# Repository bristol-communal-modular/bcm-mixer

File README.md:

# Mixer

A general purpose mixer with two mono input channels and one stereo channel.

Mono Inputs have a gain control with up to 34dB of amplification and a pan control.

Expansion header on the rear will allow additional channels to be incorporated as needed.

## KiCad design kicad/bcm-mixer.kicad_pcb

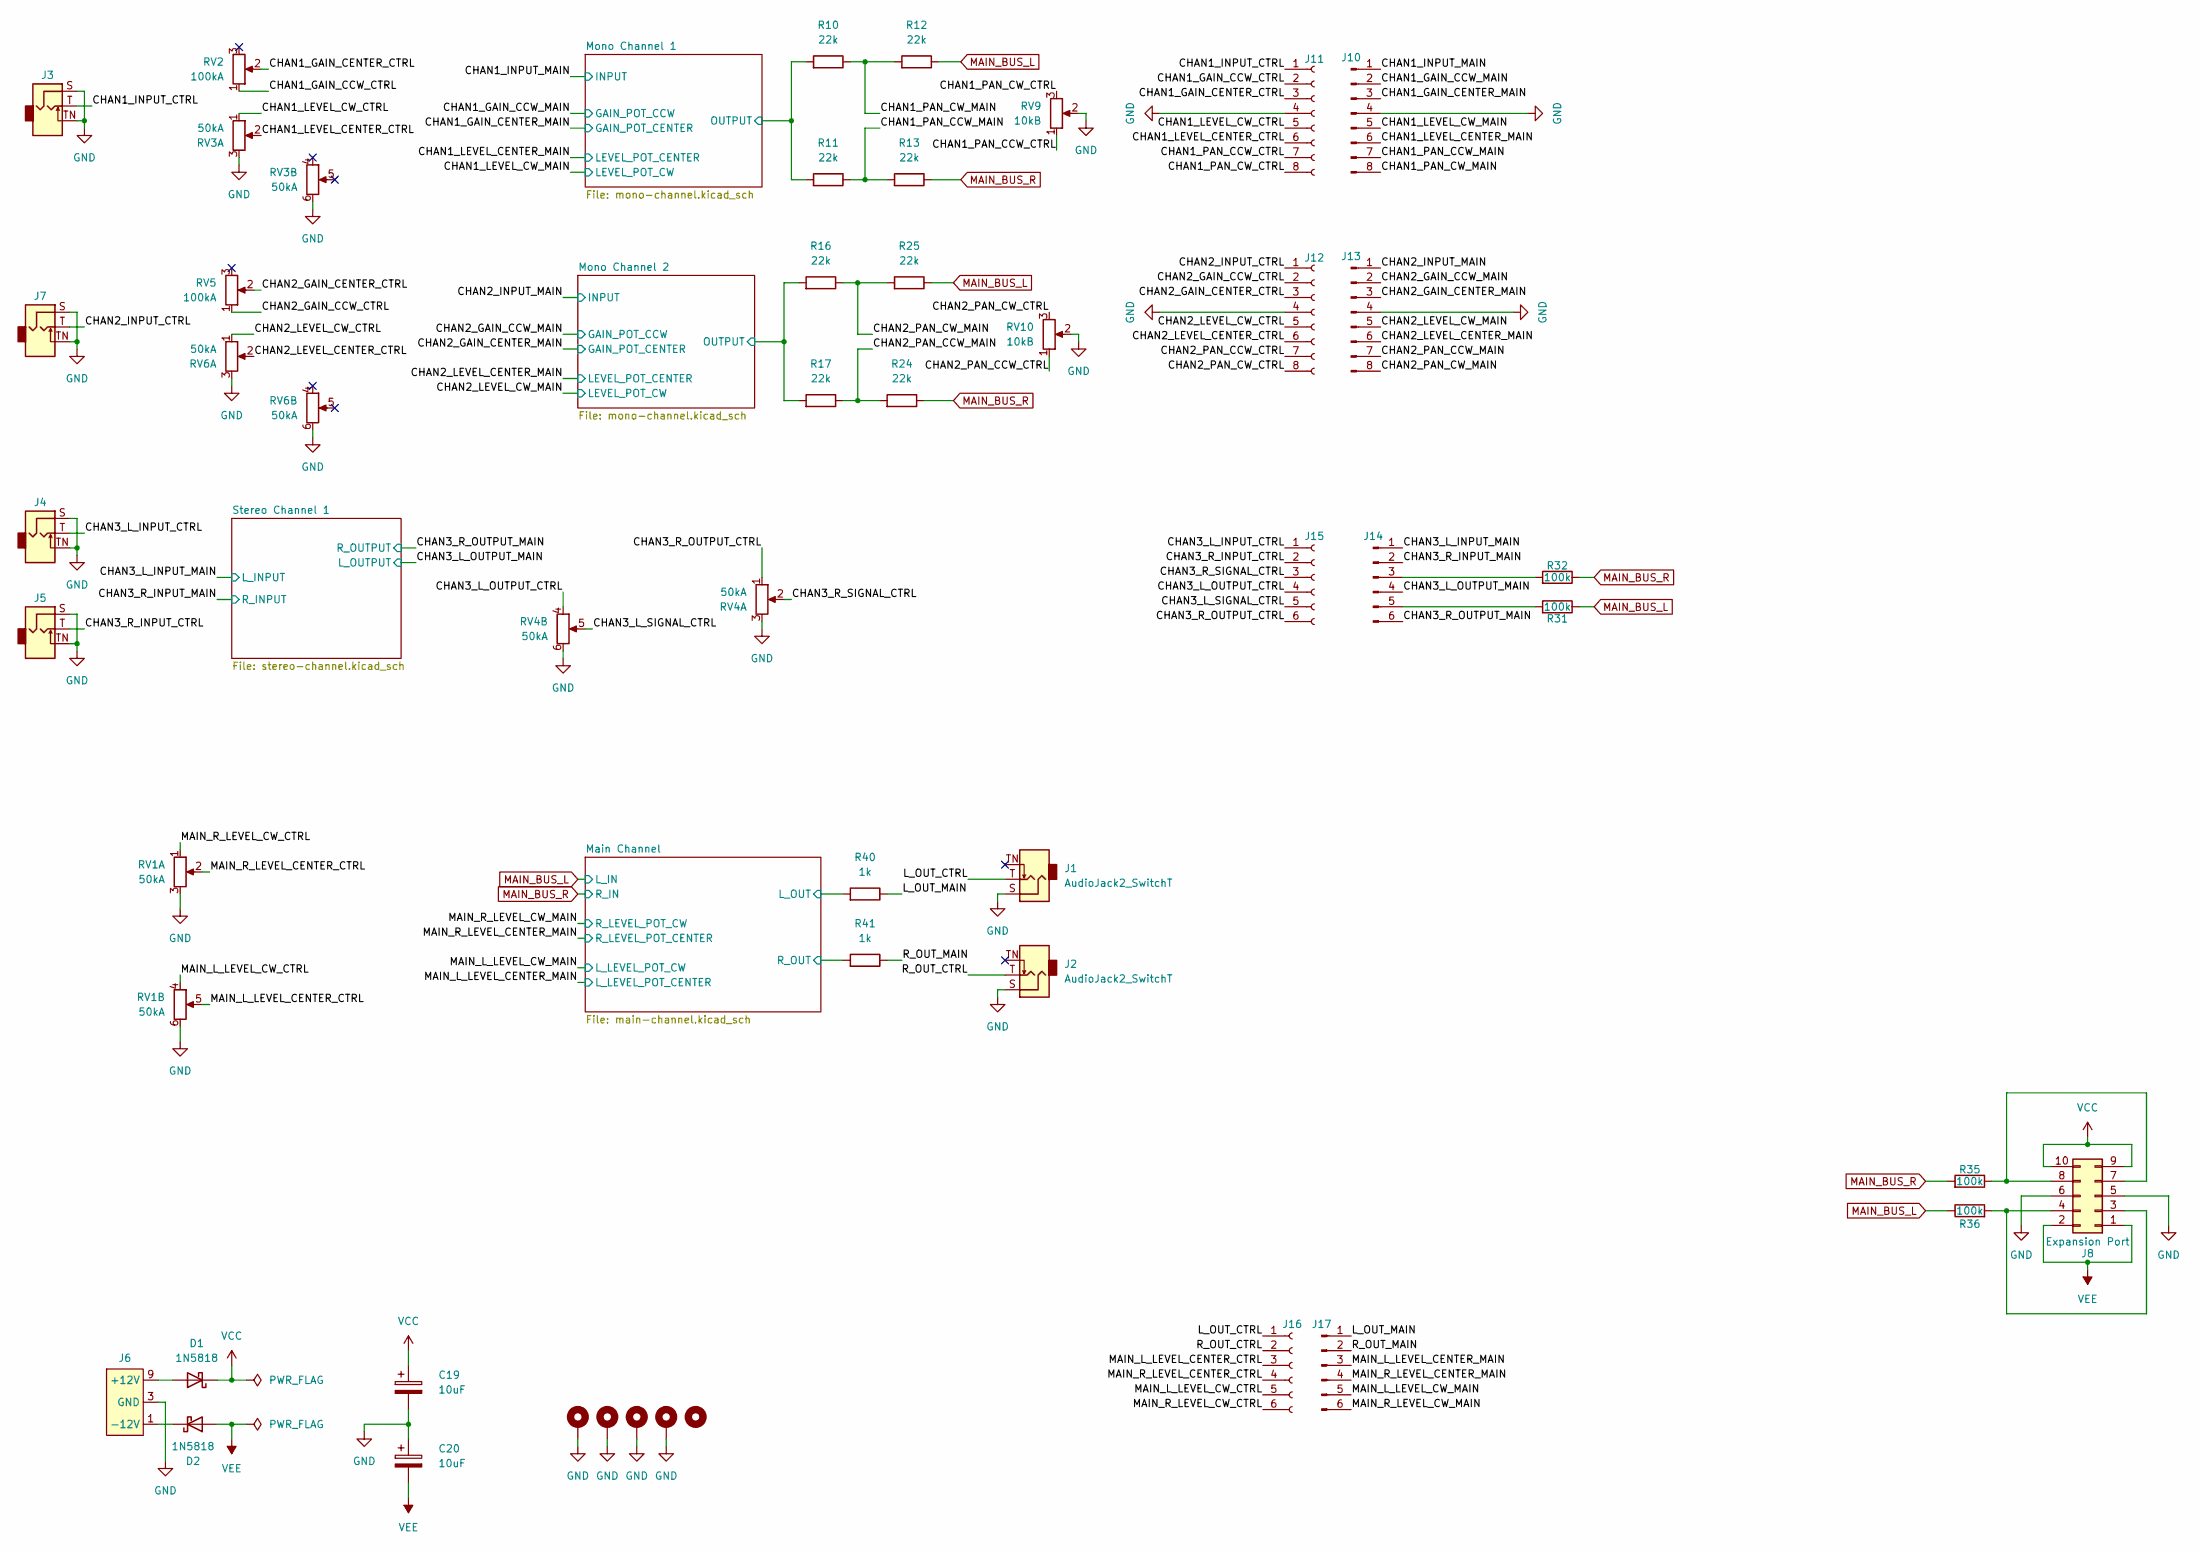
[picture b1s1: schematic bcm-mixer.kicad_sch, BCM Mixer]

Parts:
C19, C20: 10uF; CP_Radial_D5.0mm_P2.00mm; Tolerance 20%; Voltage 50v
D1, D2: 1N5818; D_DO-41_SOD81_P10.16mm_Horizontal
H1, H2, H3, H4: MountingHole_Pad; MountingHole_3.2mm_M3_DIN965_Pad
H5: MountingHole; MountingHole_3.2mm_M3_DIN965
J1, J2, J3, J4, J5, J7: AudioJack2_SwitchT; Jack_3.5mm_QingPu_WQP-PJ398SM_Vertical
J6: Eurorack Power Small; Eurorack_Power_IDC-Header_2x05_P2.54mm_Vertical
J8: Conn_02x05_Odd_Even; IDC-Header_2x05_P2.54mm_Vertical
J10, J13: Conn_01x08_Pin; PinHeader_1x08_P2.54mm_Vertical
J11, J12: Conn_01x08_Socket; PinSocket_1x08_P2.54mm_Vertical
J14, J17: Conn_01x06_Pin; PinHeader_1x06_P2.54mm_Vertical
J15, J16: Conn_01x06_Socket; PinSocket_1x06_P2.54mm_Vertical
R10, R11, R12, R13, R16, R17, R24, R25: 22k; R_Axial_DIN0207_L6.3mm_D2.5mm_P10.16mm_Horizontal; Tolerance 1%
R31, R32, R35, R36: 100k; R_Axial_DIN0207_L6.3mm_D2.5mm_P10.16mm_Horizontal; Tolerance 1%
R40, R41: 1k; R_Axial_DIN0207_L6.3mm_D2.5mm_P10.16mm_Horizontal; Tolerance 1%
RV1, RV3, RV4, RV6: 50kA; Potentiometer_TTElectronics_PS45_Dual_Frame
RV2, RV5: 100kA; Potentiometer_Alpha_RD901F-40-00D_Single_Vertical
RV9, RV10: 10kB; Potentiometer_Alpha_RD901F-40-00D_Single_Vertical

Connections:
/CHAN1_GAIN_CCW_CTRL: J11.2, RV2.1
/CHAN1_GAIN_CCW_MAIN: J10.2; also elsewhere on the board
/CHAN1_GAIN_CENTER_CTRL: J11.3, RV2.2
/CHAN1_GAIN_CENTER_MAIN: J10.3; also elsewhere on the board
/CHAN1_INPUT_CTRL: J3.T, J11.1
/CHAN1_INPUT_MAIN: J10.1; also elsewhere on the board
/CHAN1_LEVEL_CENTER_CTRL: J11.6, RV3.2
/CHAN1_LEVEL_CENTER_MAIN: J10.6; also elsewhere on the board
/CHAN1_LEVEL_CW_CTRL: J11.5, RV3.1
/CHAN1_LEVEL_CW_MAIN: J10.5; also elsewhere on the board
/CHAN1_PAN_CCW_CTRL: J11.7, RV9.1
/CHAN1_PAN_CCW_MAIN: J10.7, R11.2, R13.1
/CHAN1_PAN_CW_CTRL: J11.8, RV9.3
/CHAN1_PAN_CW_MAIN: J10.8, R10.2, R12.1
/CHAN2_GAIN_CCW_CTRL: J12.2, RV5.1
/CHAN2_GAIN_CCW_MAIN: J13.2; also elsewhere on the board
/CHAN2_GAIN_CENTER_CTRL: J12.3, RV5.2
/CHAN2_GAIN_CENTER_MAIN: J13.3; also elsewhere on the board
/CHAN2_INPUT_CTRL: J7.T, J12.1
/CHAN2_INPUT_MAIN: J13.1; also elsewhere on the board
/CHAN2_LEVEL_CENTER_CTRL: J12.6, RV6.2
/CHAN2_LEVEL_CENTER_MAIN: J13.6; also elsewhere on the board
/CHAN2_LEVEL_CW_CTRL: J12.5, RV6.1
/CHAN2_LEVEL_CW_MAIN: J13.5; also elsewhere on the board
/CHAN2_PAN_CCW_CTRL: J12.7, RV10.1
/CHAN2_PAN_CCW_MAIN: J13.7, R17.2, R24.1
/CHAN2_PAN_CW_CTRL: J12.8, RV10.3
/CHAN2_PAN_CW_MAIN: J13.8, R16.2, R25.1
/CHAN3_L_INPUT_CTRL: J4.T, J15.1
/CHAN3_L_INPUT_MAIN: J14.1; also elsewhere on the board
/CHAN3_L_OUTPUT_CTRL: J15.4, RV4.4
/CHAN3_L_OUTPUT_MAIN: J14.4; also elsewhere on the board
/CHAN3_L_SIGNAL_CTRL: J15.5, RV4.5
/CHAN3_R_INPUT_CTRL: J5.T, J15.2
/CHAN3_R_INPUT_MAIN: J14.2; also elsewhere on the board
/CHAN3_R_OUTPUT_CTRL: J15.6, RV4.1
/CHAN3_R_OUTPUT_MAIN: J14.6; also elsewhere on the board
/CHAN3_R_SIGNAL_CTRL: J15.3, RV4.2
/L_OUT_CTRL: J1.T, J16.1
/L_OUT_MAIN: J17.1, R40.2
/MAIN_L_LEVEL_CENTER_CTRL: J16.3, RV1.5
/MAIN_L_LEVEL_CENTER_MAIN: J17.3; also elsewhere on the board
/MAIN_L_LEVEL_CW_CTRL: J16.5, RV1.4
/MAIN_L_LEVEL_CW_MAIN: J17.5; also elsewhere on the board
/MAIN_R_LEVEL_CENTER_CTRL: J16.4, RV1.2
/MAIN_R_LEVEL_CENTER_MAIN: J17.4; also elsewhere on the board
/MAIN_R_LEVEL_CW_CTRL: J16.6, RV1.1
/MAIN_R_LEVEL_CW_MAIN: J17.6; also elsewhere on the board
/Main Channel/L_OUT: R40.1; also elsewhere on the board
/Main Channel/R_OUT: R41.1; also elsewhere on the board
/Mono Channel 1/OUTPUT: R10.1, R11.1; also elsewhere on the board
/Mono Channel 2/OUTPUT: R16.1, R17.1; also elsewhere on the board
/R_OUT_CTRL: J2.T, J16.2
/R_OUT_MAIN: J17.2, R41.2
GND: C19.2, C20.1, H1.1, H2.1, H3.1, H4.1, J1.S, J2.S, J3.S, J3.TN, J4.S, J4.TN, J5.S, J5.TN, J6.3 (GND), J6.4 (GND), J6.5 (GND), J6.6 (GND), J6.7 (GND), J6.8 (GND), J7.S, J7.TN, J8.5, J8.6, J10.4, J11.4, J12.4, J13.4, RV1.3, RV1.6, RV3.3, RV3.6, RV4.3, RV4.6, RV6.3, RV6.6, RV9.2, RV10.2; also elsewhere on the board
MAIN_BUS_L: R12.2, R25.2, R31.2, R35.2; also elsewhere on the board
MAIN_BUS_R: R13.2, R24.2, R32.2, R36.1; also elsewhere on the board
unnamed: D1.2 (A), J6.9 (+12V), J6.10 (+12V)
unnamed: D2.1 (K), J6.1 (-12V), J6.2 (-12V)
unnamed: J8.3, J8.4, R35.1
unnamed: J8.7, J8.8, R36.2
unnamed: J14.3, R32.1
unnamed: J14.5, R31.1
VCC: C19.1, D1.1 (K), J8.9, J8.10; also elsewhere on the board
VEE: C20.2, D2.2 (A), J8.1, J8.2; also elsewhere on the board

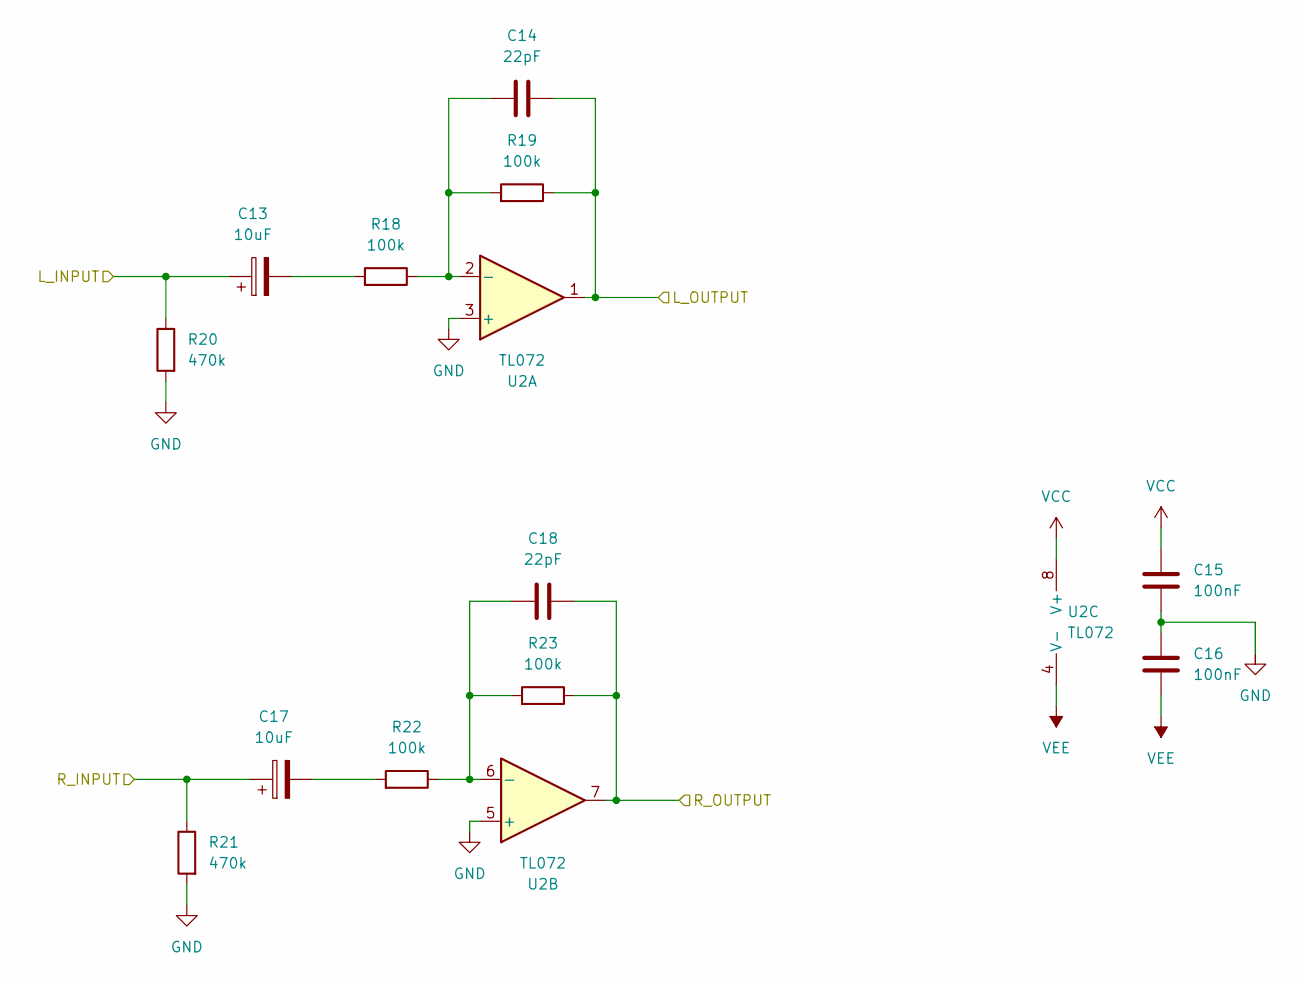
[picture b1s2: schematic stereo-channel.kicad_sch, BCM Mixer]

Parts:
C13, C17: 10uF; CP_Radial_D5.0mm_P2.00mm; Tolerance 20%; Voltage 50v
C14, C18: 22pF; C_Rect_L7.0mm_W2.5mm_P5.00mm; Tolerance 5%
C15, C16: 100nF; C_Rect_L7.0mm_W2.5mm_P5.00mm; Tolerance 5%
R18, R19, R22, R23: 100k; R_Axial_DIN0207_L6.3mm_D2.5mm_P10.16mm_Horizontal; Tolerance 1%
R20, R21: 470k; R_Axial_DIN0207_L6.3mm_D2.5mm_P10.16mm_Horizontal; Tolerance 1%
U2: TL072; DIP-8_W7.62mm_Socket

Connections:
/CHAN3_L_INPUT_MAIN: C13.1, R20.2; also elsewhere on the board
/CHAN3_L_OUTPUT_MAIN: C14.2, R19.2, U2.1; also elsewhere on the board
/CHAN3_R_INPUT_MAIN: C17.1, R21.2; also elsewhere on the board
/CHAN3_R_OUTPUT_MAIN: C18.2, R23.2, U2.7; also elsewhere on the board
GND: C15.1, C16.2, R20.1, R21.1, U2.3 (+), U2.5 (+); also elsewhere on the board
unnamed: C13.2, R18.1
unnamed: C17.2, R22.1
unnamed: C14.1, R18.2, R19.1, U2.2 (-)
unnamed: C18.1, R22.2, R23.1, U2.6 (-)
VCC: C15.2, U2.8 (V+); also elsewhere on the board
VEE: C16.1, U2.4 (V-); also elsewhere on the board

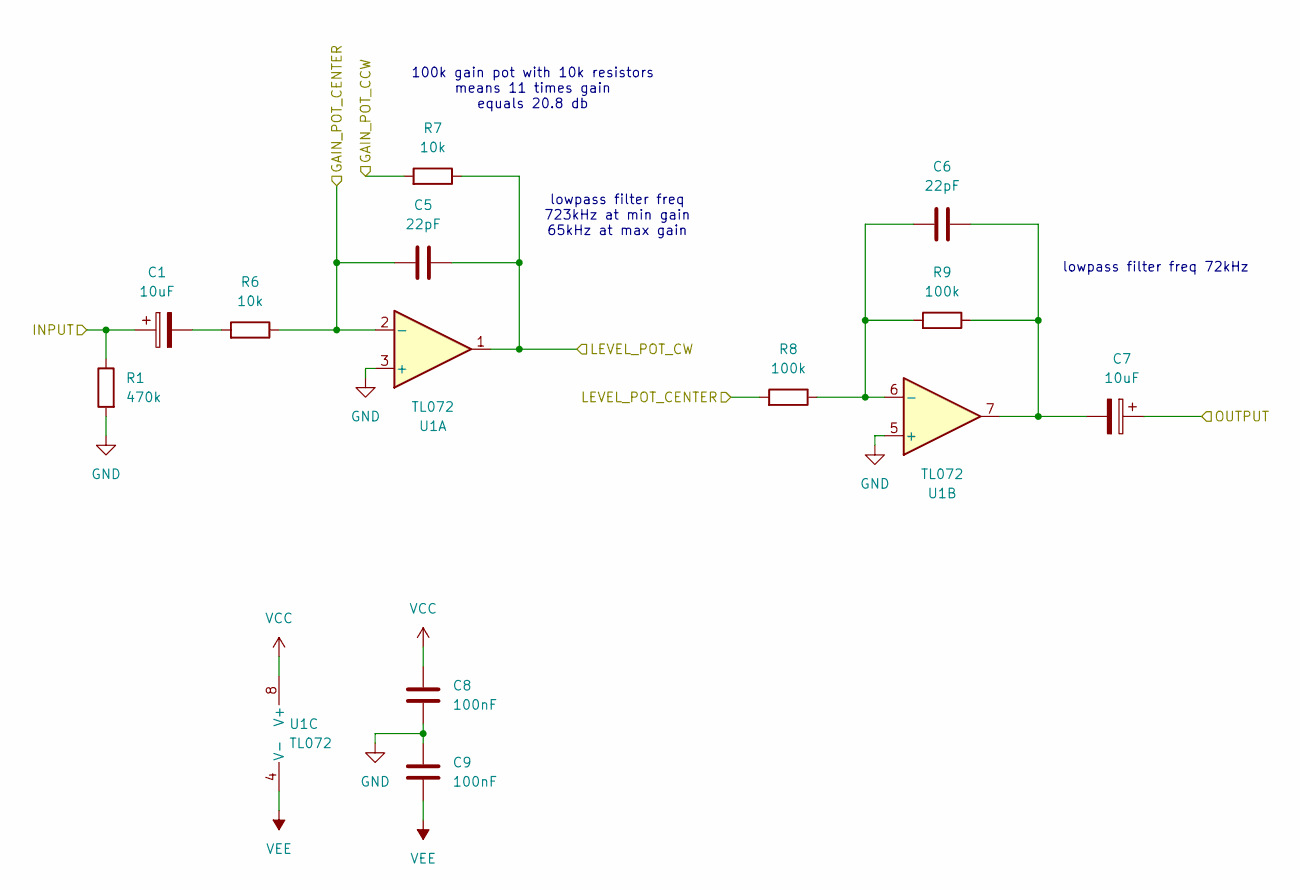
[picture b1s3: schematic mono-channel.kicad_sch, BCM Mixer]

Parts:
C1, C7: 10uF; CP_Radial_D5.0mm_P2.00mm; Tolerance 20%; Voltage 50v
C5, C6: 22pF; C_Rect_L7.0mm_W2.5mm_P5.00mm; Tolerance 5%
C8, C9: 100nF; C_Rect_L7.0mm_W2.5mm_P5.00mm; Tolerance 5%
R1: 470k; R_Axial_DIN0207_L6.3mm_D2.5mm_P10.16mm_Horizontal; Tolerance 1%
R6, R7: 10k; R_Axial_DIN0207_L6.3mm_D2.5mm_P10.16mm_Horizontal; Tolerance 1%
R8, R9: 100k; R_Axial_DIN0207_L6.3mm_D2.5mm_P10.16mm_Horizontal; Tolerance 1%
U1: TL072; DIP-8_W7.62mm_Socket

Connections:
/CHAN1_GAIN_CCW_MAIN: R7.1; also elsewhere on the board
/CHAN1_GAIN_CENTER_MAIN: C5.1, R6.2, U1.2 (-); also elsewhere on the board
/CHAN1_INPUT_MAIN: C1.1, R1.2; also elsewhere on the board
/CHAN1_LEVEL_CENTER_MAIN: R8.1; also elsewhere on the board
/CHAN1_LEVEL_CW_MAIN: C5.2, R7.2, U1.1; also elsewhere on the board
/Mono Channel 1/OUTPUT: C7.1; also elsewhere on the board
GND: C8.1, C9.2, R1.1, U1.3 (+), U1.5 (+); also elsewhere on the board
unnamed: C1.2, R6.1
unnamed: C6.2, C7.2, R9.2, U1.7
unnamed: C6.1, R8.2, R9.1, U1.6 (-)
VCC: C8.2, U1.8 (V+); also elsewhere on the board
VEE: C9.1, U1.4 (V-); also elsewhere on the board

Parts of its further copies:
C21, C26: 10uF; CP_Radial_D5.0mm_P2.00mm; Tolerance 20%; Voltage 50v
C22, C25: 22pF; C_Rect_L7.0mm_W2.5mm_P5.00mm; Tolerance 5%
C23, C24: 100nF; C_Rect_L7.0mm_W2.5mm_P5.00mm; Tolerance 5%
R26: 470k; R_Axial_DIN0207_L6.3mm_D2.5mm_P10.16mm_Horizontal; Tolerance 1%
R27, R28: 10k; R_Axial_DIN0207_L6.3mm_D2.5mm_P10.16mm_Horizontal; Tolerance 1%
R29, R30: 100k; R_Axial_DIN0207_L6.3mm_D2.5mm_P10.16mm_Horizontal; Tolerance 1%
U4: TL072; DIP-8_W7.62mm_Socket

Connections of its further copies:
/CHAN2_GAIN_CCW_MAIN: R28.1; also elsewhere on the board
/CHAN2_GAIN_CENTER_MAIN: C22.1, R27.2, U4.2 (-); also elsewhere on the board
/CHAN2_INPUT_MAIN: C21.1, R26.2; also elsewhere on the board
/CHAN2_LEVEL_CENTER_MAIN: R29.1; also elsewhere on the board
/CHAN2_LEVEL_CW_MAIN: C22.2, R28.2, U4.1; also elsewhere on the board
/Mono Channel 2/OUTPUT: C26.1; also elsewhere on the board
GND: C23.1, C24.2, R26.1, U4.3 (+), U4.5 (+); also elsewhere on the board
unnamed: C21.2, R27.1
unnamed: C25.2, C26.2, R30.2, U4.7
unnamed: C25.1, R29.2, R30.1, U4.6 (-)
VCC: C23.2, U4.8 (V+); also elsewhere on the board
VEE: C24.1, U4.4 (V-); also elsewhere on the board

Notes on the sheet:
100k gain pot with 10k resistors means 11 times gain equals 20.8 db
lowpass filter freq 72kHz
lowpass filter freq 723kHz at min gain 65kHz at max gain

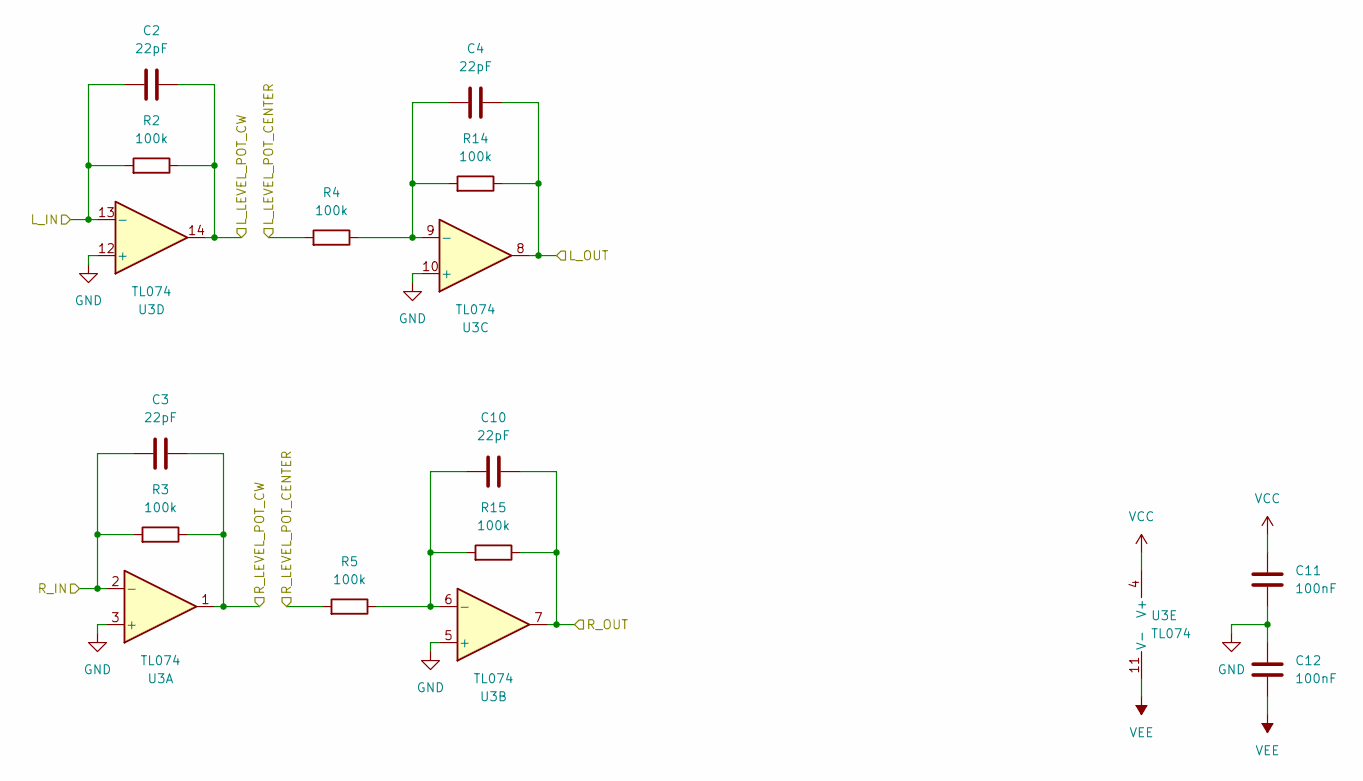
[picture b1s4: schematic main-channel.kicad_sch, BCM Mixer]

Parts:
C2, C3, C4, C10: 22pF; C_Rect_L7.0mm_W2.5mm_P5.00mm; Tolerance 5%
C11, C12: 100nF; C_Rect_L7.0mm_W2.5mm_P5.00mm; Tolerance 5%
R2, R3, R4, R5, R14, R15: 100k; R_Axial_DIN0207_L6.3mm_D2.5mm_P10.16mm_Horizontal; Tolerance 1%
U3: TL074; DIP-14_W7.62mm_Socket_LongPads

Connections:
/MAIN_L_LEVEL_CENTER_MAIN: R4.1; also elsewhere on the board
/MAIN_L_LEVEL_CW_MAIN: C2.2, R2.2, U3.14; also elsewhere on the board
/MAIN_R_LEVEL_CENTER_MAIN: R5.1; also elsewhere on the board
/MAIN_R_LEVEL_CW_MAIN: C3.2, R3.2, U3.1; also elsewhere on the board
/Main Channel/L_OUT: C4.2, R14.2, U3.8; also elsewhere on the board
/Main Channel/R_OUT: C10.2, R15.2, U3.7; also elsewhere on the board
GND: C11.1, C12.2, U3.3 (+), U3.5 (+), U3.10 (+), U3.12 (+); also elsewhere on the board
MAIN_BUS_L: C2.1, R2.1, U3.13 (-); also elsewhere on the board
MAIN_BUS_R: C3.1, R3.1, U3.2 (-); also elsewhere on the board
unnamed: C10.1, R5.2, R15.1, U3.6 (-)
unnamed: C4.1, R4.2, R14.1, U3.9 (-)
VCC: C11.2, U3.4 (V+); also elsewhere on the board
VEE: C12.1, U3.11 (V-); also elsewhere on the board

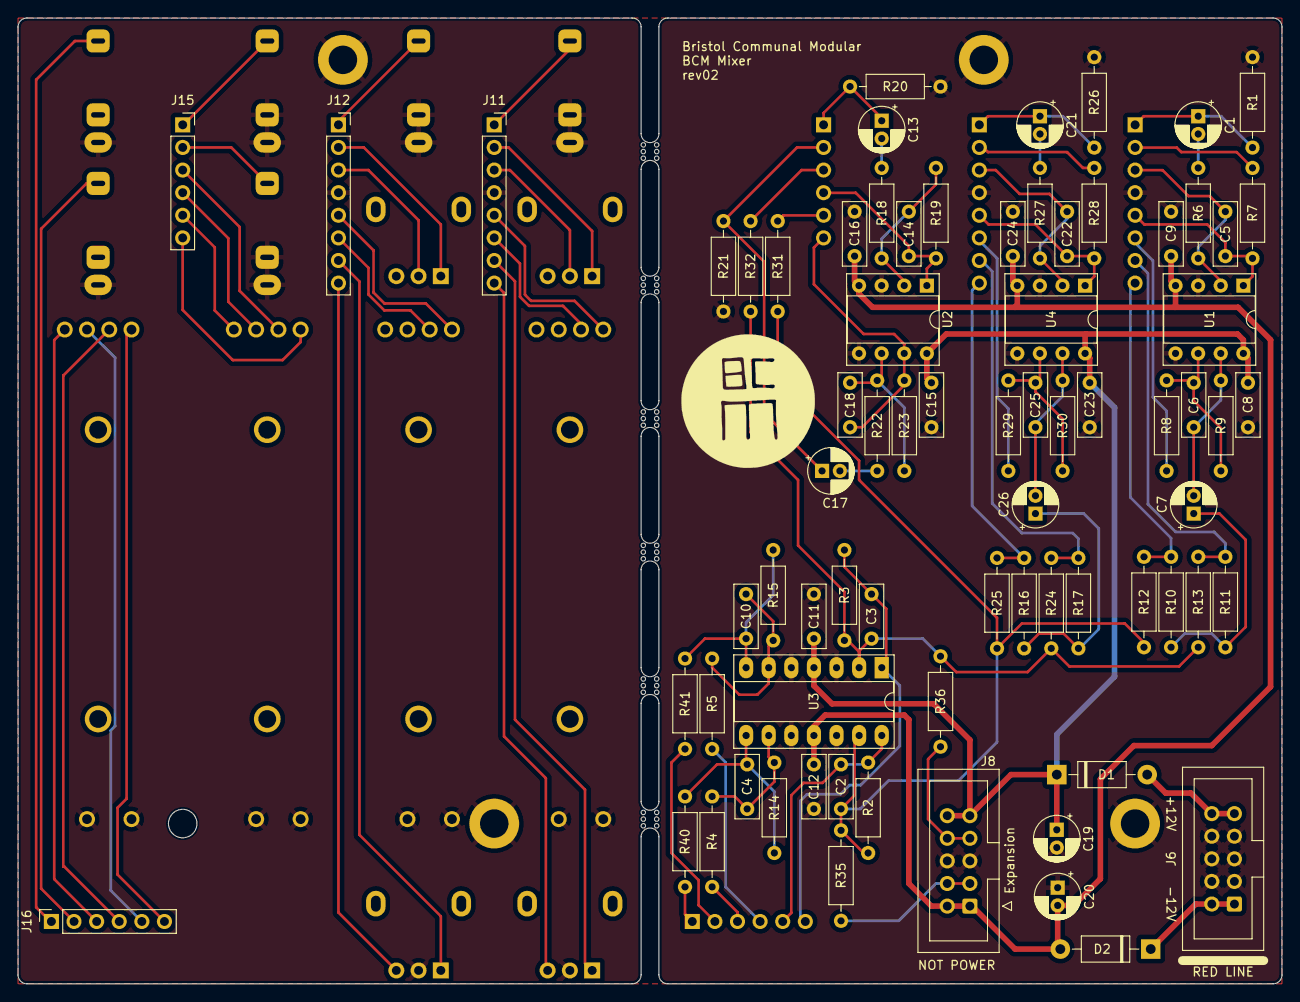
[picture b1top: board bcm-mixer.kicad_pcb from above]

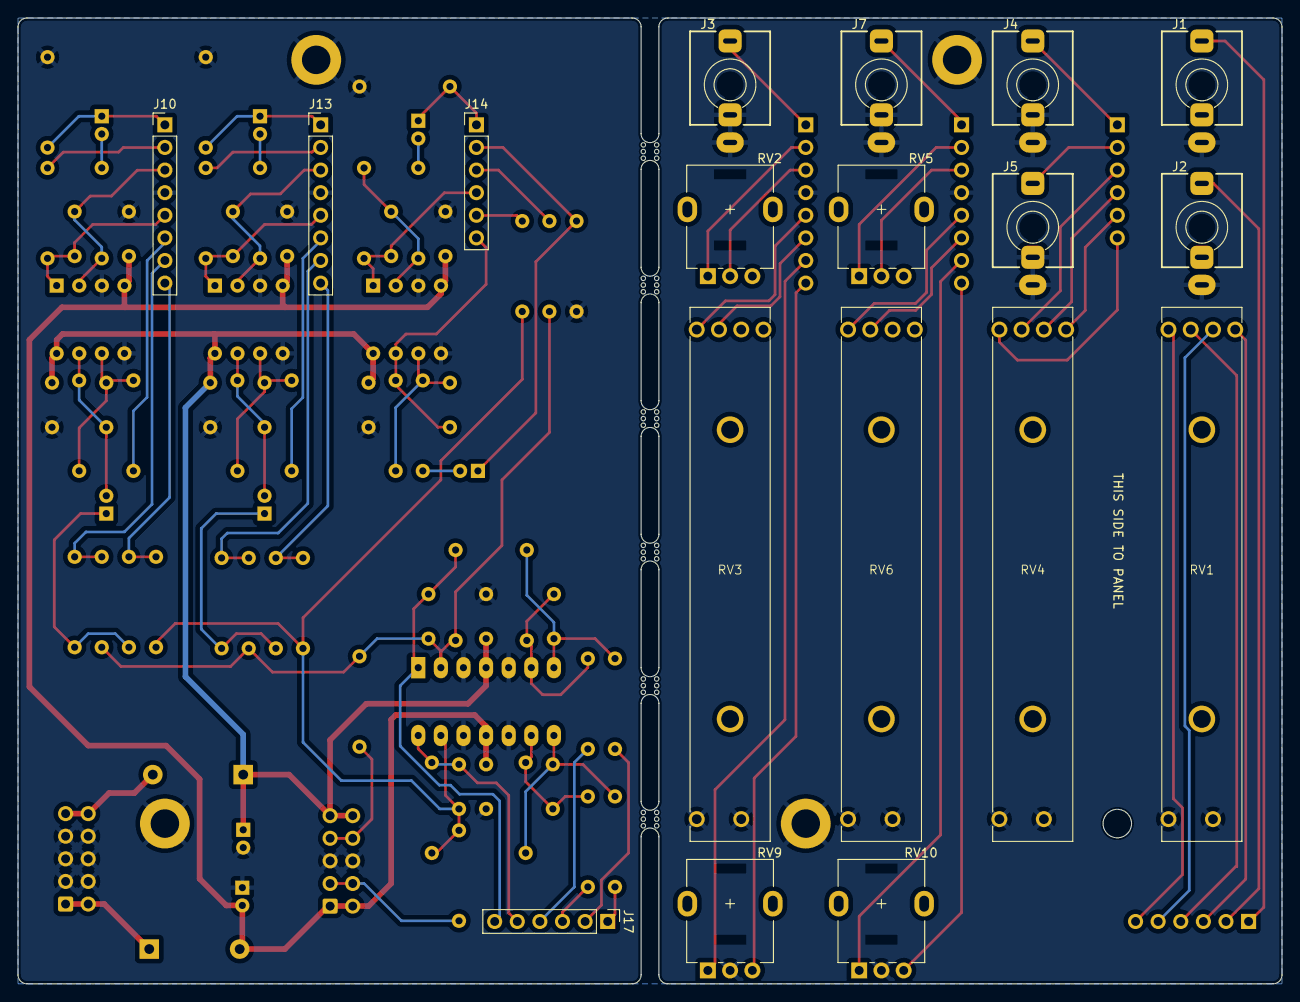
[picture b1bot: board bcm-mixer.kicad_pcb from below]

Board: 2 copper layers, 142.0 x 108.5 mm, 104 parts (18 on the bottom side), 77 nets.

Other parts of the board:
Ref**: Val**; BCM_Logo_small_15mmx15mm
mouse-bite-2mm-slot, mouse-bite-2mm-slot#2, mouse-bite-2mm-slot#3, mouse-bite-2mm-slot#4, mouse-bite-2mm-slot#5, mouse-bite-2mm-slot#6: VAL**; mouse-bite-2mm-slot

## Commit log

2024-12-05 Updating everything and adding gerbers
2024-12-05 Adding interactive BOMt
2024-12-19 Regenerating gerbers
2025-01-19 Updating power header symbol
2025-01-22 Update slide pot values based on what's actually available
2025-02-16 Updating for revision 2

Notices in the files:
kicad/bcm-mixer.kicad_pcb:
creativecommons.org/licenses/by/4.0
License: CC BY 4.0
